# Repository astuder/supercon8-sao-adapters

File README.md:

We love the [Hackaday Supercon 8 Add On Badge](https://github.com/Hack-a-Day/2024-Supercon-8-Add-On-Badge),
but in our opinion it has two major design flaws:
1. 4 out of 6 SAO slots are oriented sideways or upside-down
2. there is a large empty area in the center of the badge

We present two simple adapters to solve these issues.

(see note below for links to the SAOs shown)

**SAO Up** rotates the SAO slot by 90 degrees, orienting SAOs closer to
their upright position. The same PCB works for the left and right side
of the badge, depending on which side the SAO headers are soldered.

**SAO Bridge** adds an SAO slot in the center of the badge, and also
rotates the left and right SAO slots into upright orientation. The center
slot is connected to power and I2C of the bus on the left side of the
badge (slot 2).

Black would have been the logical color for the adapters. But we only had
10 days between [badge reveal](https://hackaday.com/2024/10/22/the-2024-hackaday-supercon-sao-badge-reveal/)
and the event, so we went with green as that offered the fastest
turnaround time at JLCPCB.

You are welcome to duplicate, adapt or steal this project. The license is
CERN-OHL-P, which is open and permissive.

**SAOs used for demo**

Here's a list of the SAOs shown in the photos above:
* [duckGLOW](https://hackaday.io/project/198918-duckglow-sao) by myself
* [Hack-Man](https://hackaday.io/project/198301-hack-man-sao) by InstantArcade
* [Featuring You!](https://hackaday.io/project/198924-featuring-you) by Nanik Adnani
* [Yo Dawg](https://hackaday.io/project/198060-yo-dawg-sao-introducing-saoao) by davedarko
* [Infinity Mirror](https://hackaday.io/project/198943-sao-infinity-mirror) by Scorch Works
* [Wolverine](https://mastodon.social/@simenzhor/113266947534371773) by Simen E. Sørensen

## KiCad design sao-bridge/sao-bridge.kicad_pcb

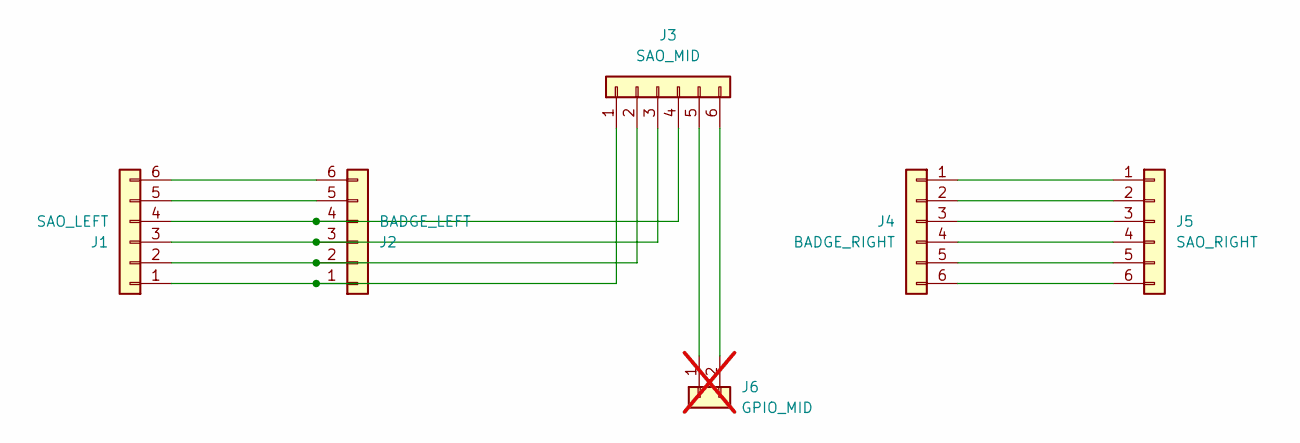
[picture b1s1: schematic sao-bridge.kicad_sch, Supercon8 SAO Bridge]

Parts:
J1: SAO_LEFT; PinSocket_2x03_P2.54mm_Vertical
J2: BADGE_LEFT; PinHeader_2x03_P2.54mm_Vertical
J3: SAO_MID; PinSocket_2x03_P2.54mm_Vertical
J4: BADGE_RIGHT; PinHeader_2x03_P2.54mm_Vertical
J5: SAO_RIGHT; PinSocket_2x03_P2.54mm_Vertical
J6: GPIO_MID; PinHeader_1x02_P2.54mm_Vertical; not fitted

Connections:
unnamed: J1.1, J2.1, J3.1
unnamed: J1.2, J2.2, J3.2
unnamed: J1.3, J2.3, J3.3
unnamed: J1.4, J2.4, J3.4
unnamed: J1.5, J2.5
unnamed: J1.6, J2.6
unnamed: J3.5, J6.1
unnamed: J3.6, J6.2
unnamed: J4.1, J5.1
unnamed: J4.2, J5.2
unnamed: J4.3, J5.3
unnamed: J4.4, J5.4
unnamed: J4.5, J5.5
unnamed: J4.6, J5.6

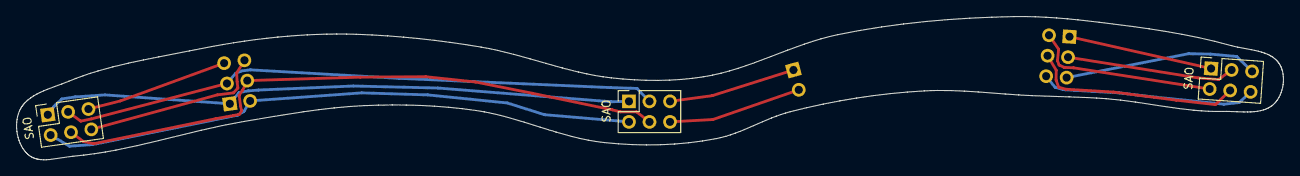
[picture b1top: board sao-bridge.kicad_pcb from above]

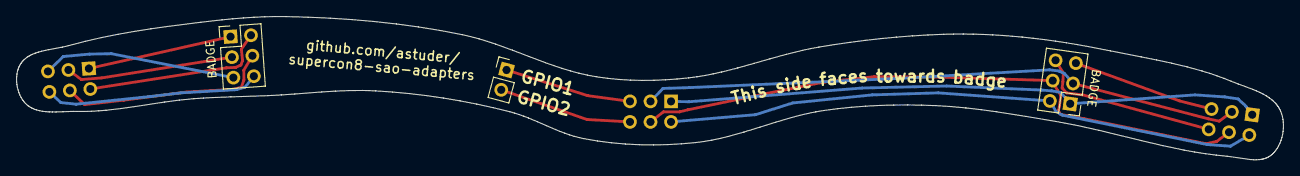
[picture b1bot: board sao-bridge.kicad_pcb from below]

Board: 2 copper layers, 156.8 x 17.7 mm, 6 parts (3 on the bottom side), 14 nets.

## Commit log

2025-01-12 fix image link
2025-01-12 fix typo
2025-01-13 add some info to bottom siklscreen
2025-01-13 bump version
2025-01-13 add references to SAO shown
2025-01-13 add references to SAOs shown
